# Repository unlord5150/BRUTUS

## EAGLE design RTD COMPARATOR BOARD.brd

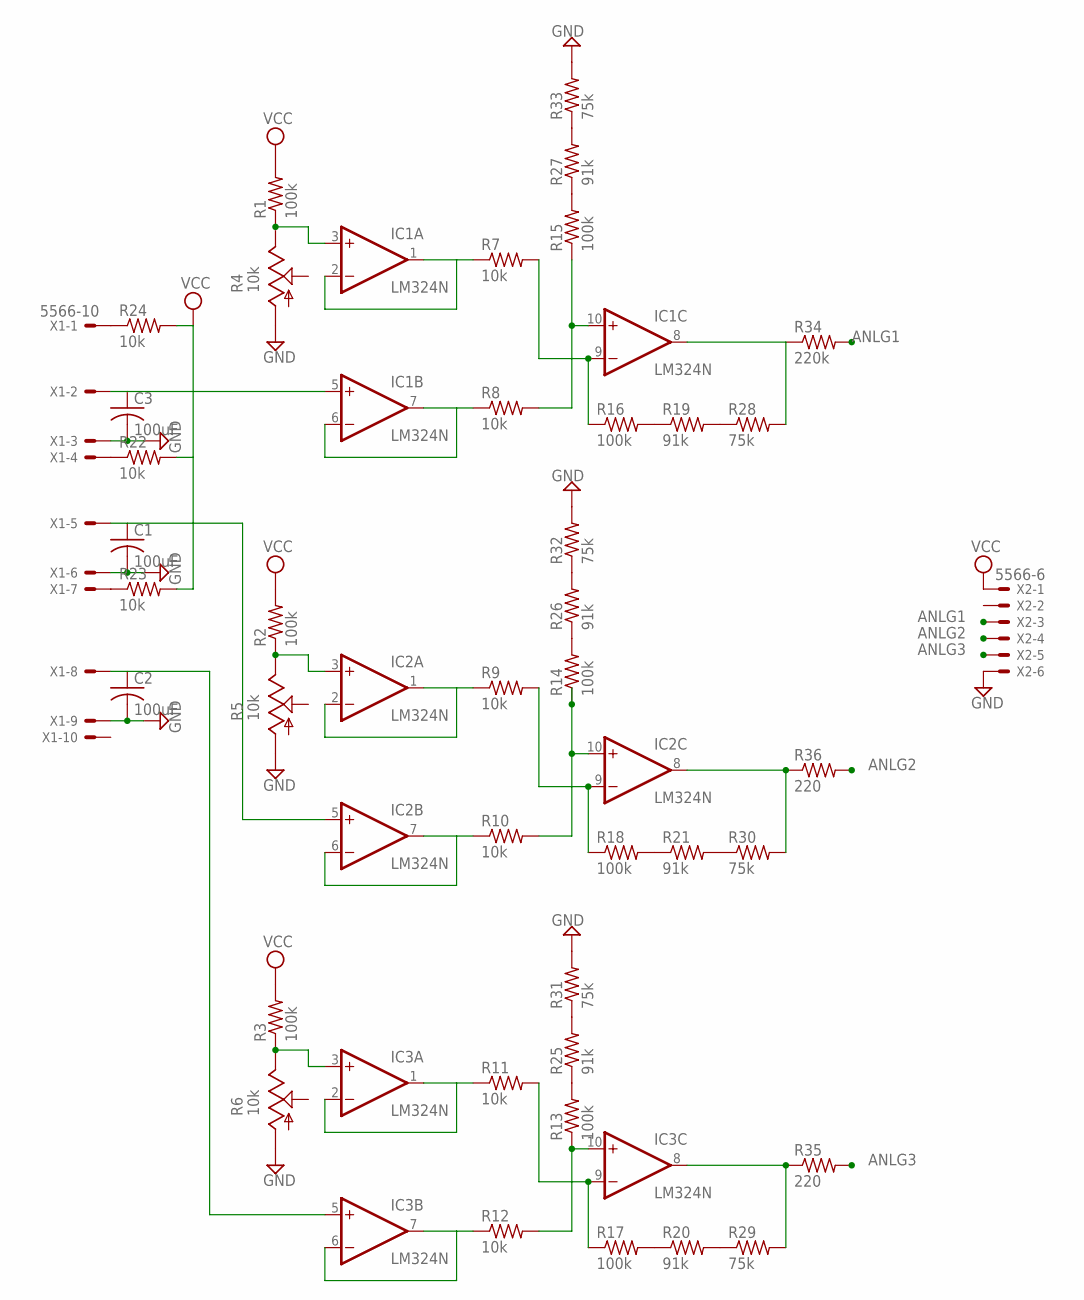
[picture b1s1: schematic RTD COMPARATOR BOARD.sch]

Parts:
C1, C2, C3: 100uF; C025-025X050
IC1, IC2, IC3: LM324N; DIL14
R1, R2, R3, R13, R14, R15, R16, R17, R18: 100k; 0204V
R4, R5, R6: 10k; B25P
R7, R8, R9, R10, R11, R12, R22, R23, R24: 10k; 0204V
R19, R20, R21, R25, R26, R27: 91k; 0204V
R28, R29, R30, R31, R32, R33: 75k; 0204V
R34: 220k; 0204V
R35, R36: 220; 0204V
X1: 5566-10
X2: 5566-6

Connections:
ANLG1: R34.2, X2.3
ANLG2: R36.2, X2.4
ANLG3: R35.2, X2.5
GND: C1.2, C2.2, C3.2, R4.A, R5.A, R6.A, R31.2, R32.2, R33.2, X1.3, X1.6, X1.9, X2.6
unnamed: R21.2, R30.1
unnamed: R18.2, R21.1
unnamed: R24.1, X1.1
unnamed: R22.1, X1.4
unnamed: R20.2, R29.1
unnamed: R17.2, R20.1
unnamed: R14.2, R26.1
unnamed: R26.2, R32.1
unnamed: IC2.3 (+IN), R2.1, R5.E
unnamed: R23.1, X1.7
unnamed: R13.2, R25.1
unnamed: IC1.3 (+IN), R1.1, R4.E
unnamed: C1.1, X1.5
unnamed: IC2.1 (OUT), IC2.2 (-IN), R9.1
unnamed: IC2.9 (-IN), R9.2, R18.1
unnamed: R25.2, R31.1
unnamed: IC1.9 (-IN), R7.2, R16.1
unnamed: IC1.1 (OUT), IC1.2 (-IN), R7.1
unnamed: IC2.6 (-IN), IC2.7 (OUT), R10.1
unnamed: IC1.6 (-IN), IC1.7 (OUT), R8.1
unnamed: IC1.10 (+IN), R8.2, R15.1
unnamed: IC1.8 (OUT), R28.2, R34.1
unnamed: C3.1, IC1.5 (+IN), X1.2
unnamed: IC2.10 (+IN), R10.2, R14.1
unnamed: R19.2, R28.1
unnamed: R16.2, R19.1
unnamed: IC2.8 (OUT), R30.2, R36.1
unnamed: R15.2, R27.1
unnamed: R27.2, R33.1
unnamed: IC3.3 (+IN), R3.1, R6.E
unnamed: IC3.1 (OUT), IC3.2 (-IN), R11.1
unnamed: IC3.9 (-IN), R11.2, R17.1
unnamed: IC3.6 (-IN), IC3.7 (OUT), R12.1
unnamed: IC3.10 (+IN), R12.2, R13.1
unnamed: IC3.8 (OUT), R29.2, R35.1
V+: IC1.4 (V+), IC2.4 (V+), IC3.4 (V+)
V-: IC1.11 (V-), IC2.11 (V-), IC3.11 (V-)
VCC: R1.2, R2.2, R3.2, R22.2, R23.2, R24.2, X2.1

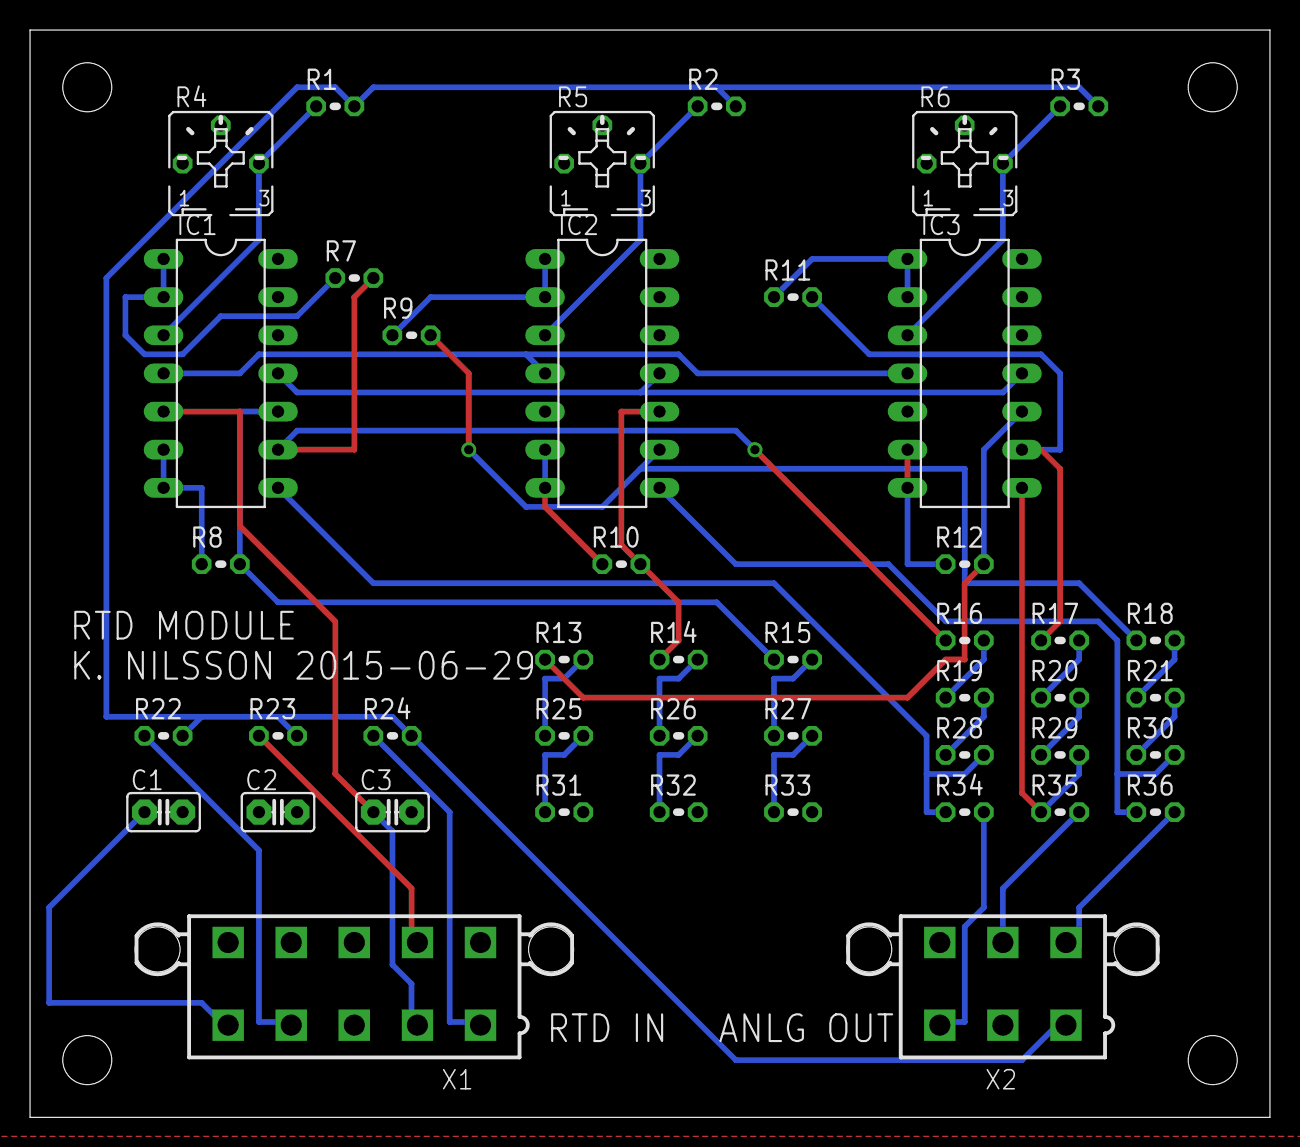
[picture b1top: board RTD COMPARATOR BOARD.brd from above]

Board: 2 copper layers, 82.5 x 72.4 mm, 44 parts (0 on the bottom side), 42 nets.

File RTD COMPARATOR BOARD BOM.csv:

"Part";"Value";"Device";"Package";"Description";"MF";"MPN";"OC_FARNELL";"OC_NEWARK";
"C1";"100uF";"C-US025-025X050";"C025-025X050";"CAPACITOR, American symbol";"";"";"";"";
"C2";"100uF";"C-US025-025X050";"C025-025X050";"CAPACITOR, American symbol";"";"";"";"";
"C3";"100uF";"C-US025-025X050";"C025-025X050";"CAPACITOR, American symbol";"";"";"";"";
"IC1";"LM324N";"LM324N";"DIL14";"OP AMP";"";"";"";"";
"IC2";"LM324N";"LM324N";"DIL14";"OP AMP";"";"";"";"";
"IC3";"LM324N";"LM324N";"DIL14";"OP AMP";"";"";"";"";
"IC4";"LM324N";"LM324N";"DIL14";"OP AMP";"";"";"";"";
"IC5";"LM324N";"LM324N";"DIL14";"OP AMP";"";"";"";"";
"IC6";"LM324N";"LM324N";"DIL14";"OP AMP";"";"";"";"";
"IC7";"LM324N";"LM324N";"DIL14";"OP AMP";"";"";"";"";
"IC8";"LM324N";"LM324N";"DIL14";"OP AMP";"";"";"";"";
"IC9";"LM324N";"LM324N";"DIL14";"OP AMP";"";"";"";"";
"R1";"100k";"R-US_0204/2V";"0204V";"RESISTOR, American symbol";"";"";"";"";
"R2";"100k";"R-US_0204/2V";"0204V";"RESISTOR, American symbol";"";"";"";"";
"R3";"100k";"R-US_0204/2V";"0204V";"RESISTOR, American symbol";"";"";"";"";
"R4";"10k";"TRIM_US-B25P";"B25P";"POTENTIOMETER";"";"";"";"";
"R5";"10k";"TRIM_US-B25P";"B25P";"POTENTIOMETER";"";"";"";"";
"R6";"10k";"TRIM_US-B25P";"B25P";"POTENTIOMETER";"";"";"";"";
"R7";"10k";"R-US_0204/2V";"0204V";"RESISTOR, American symbol";"";"";"";"";
"R8";"10k";"R-US_0204/2V";"0204V";"RESISTOR, American symbol";"";"";"";"";
"R9";"10k";"R-US_0204/2V";"0204V";"RESISTOR, American symbol";"";"";"";"";
"R10";"10k";"R-US_0204/2V";"0204V";"RESISTOR, American symbol";"";"";"";"";
"R11";"10k";"R-US_0204/2V";"0204V";"RESISTOR, American symbol";"";"";"";"";
"R12";"10k";"R-US_0204/2V";"0204V";"RESISTOR, American symbol";"";"";"";"";
"R13";"100k";"R-US_0204/2V";"0204V";"RESISTOR, American symbol";"";"";"";"";
"R14";"100k";"R-US_0204/2V";"0204V";"RESISTOR, American symbol";"";"";"";"";
"R15";"100k";"R-US_0204/2V";"0204V";"RESISTOR, American symbol";"";"";"";"";
"R16";"100k";"R-US_0204/2V";"0204V";"RESISTOR, American symbol";"";"";"";"";
"R17";"100k";"R-US_0204/2V";"0204V";"RESISTOR, American symbol";"";"";"";"";
"R18";"100k";"R-US_0204/2V";"0204V";"RESISTOR, American symbol";"";"";"";"";
"R19";"91k";"R-US_0204/2V";"0204V";"RESISTOR, American symbol";"";"";"";"";
"R20";"91k";"R-US_0204/2V";"0204V";"RESISTOR, American symbol";"";"";"";"";
"R21";"91k";"R-US_0204/2V";"0204V";"RESISTOR, American symbol";"";"";"";"";
"R22";"1k";"R-US_0204/2V";"0204V";"RESISTOR, American symbol";"";"";"";"";
"R23";"1k";"R-US_0204/2V";"0204V";"RESISTOR, American symbol";"";"";"";"";
"R24";"1k";"R-US_0204/2V";"0204V";"RESISTOR, American symbol";"";"";"";"";
"R25";"91k";"R-US_0204/2V";"0204V";"RESISTOR, American symbol";"";"";"";"";
"R26";"91k";"R-US_0204/2V";"0204V";"RESISTOR, American symbol";"";"";"";"";
"R27";"91k";"R-US_0204/2V";"0204V";"RESISTOR, American symbol";"";"";"";"";
"R28";"75k";"R-US_0204/2V";"0204V";"RESISTOR, American symbol";"";"";"";"";
"R29";"75k";"R-US_0204/2V";"0204V";"RESISTOR, American symbol";"";"";"";"";
"R30";"75k";"R-US_0204/2V";"0204V";"RESISTOR, American symbol";"";"";"";"";
"R31";"75k";"R-US_0204/2V";"0204V";"RESISTOR, American symbol";"";"";"";"";
"R32";"75k";"R-US_0204/2V";"0204V";"RESISTOR, American symbol";"";"";"";"";
"R33";"75k";"R-US_0204/2V";"0204V";"RESISTOR, American symbol";"";"";"";"";
"R34";"220";"R-US_0204/2V";"0204V";"RESISTOR, American symbol";"";"";"";"";
"R35";"220";"R-US_0204/2V";"0204V";"RESISTOR, American symbol";"";"";"";"";
"R36";"220";"R-US_0204/2V";"0204V";"RESISTOR, American symbol";"";"";"";"";
"X1";"5566-10";"5566-10";"5566-10";"Mini FIT connector 10 pol";"";"";"unknown";"unknown";
"X2";"5566-6";"5566-6";"5566-6";"Mini FIT connector 6 pol";"";"95566-61002";"unknown";"22K8620";

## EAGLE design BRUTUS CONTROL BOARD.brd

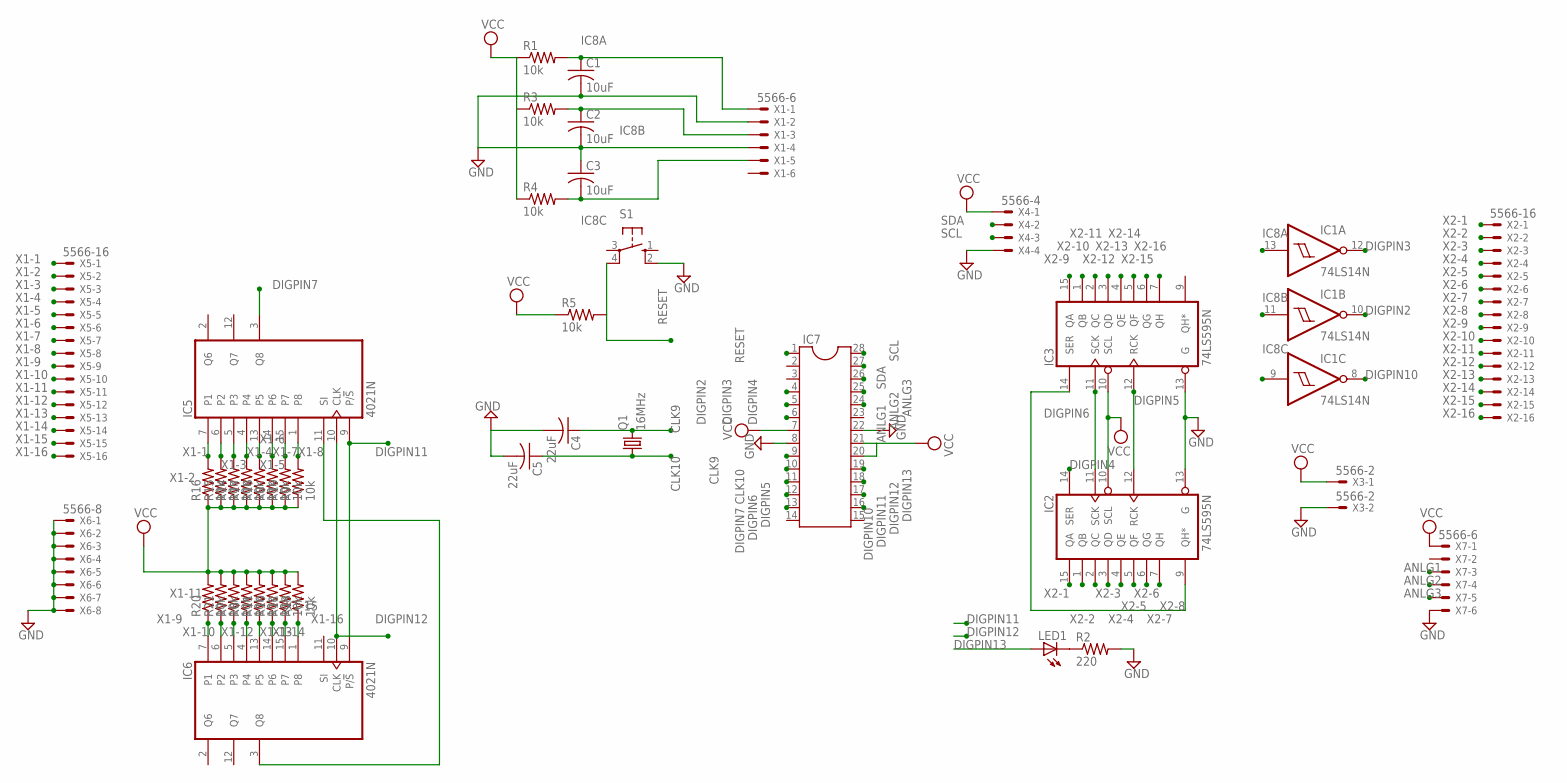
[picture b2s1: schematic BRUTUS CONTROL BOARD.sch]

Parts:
C1, C2, C3: 10uF; C025-025X050
C4, C5: 22uF; C025-025X050
IC1: 74LS14N; DIL14
IC2, IC3: 74LS595N; DIL16
IC5, IC6: 4021N; DIL16
IC7: DIL28-3
LED1: LED5MM
Q1: 16MHz; HC49/S
R1, R3, R4, R5, R6, R7, R8, R9, R10, R11, R12, R13, R14, R15, R16, R17, R18, R19, R20, R21: 10k; 0204V
R2: 220; 0204V
S1: 40-XX; B3F-40XX
X1, X7: 5566-6
X2, X5: 5566-16
X3: 5566-2
X4: 5566-4
X6: 5566-8

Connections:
ANLG1: IC7.24, X7.3
ANLG2: IC7.25, X7.4
ANLG3: IC7.26, X7.5
CLK9: C4.1, IC7.9, Q1.2
CLK10: C5.1, IC7.10, Q1.1
DIGPIN2: IC1.10 (O), IC7.4
DIGPIN3: IC1.12 (O), IC7.5
DIGPIN4: IC2.14 (SER), IC7.6
DIGPIN5: IC2.12 (RCK), IC3.12 (RCK), IC7.11
DIGPIN6: IC2.11 (SCK), IC3.11 (SCK), IC7.12
DIGPIN7: IC5.3 (Q8), IC7.13
DIGPIN10: IC1.8 (O), IC7.16
DIGPIN11: IC5.9 (P/!S), IC6.9 (P/!S), IC7.17
DIGPIN12: IC5.10 (CLK), IC6.10 (CLK), IC7.18
DIGPIN13: IC7.19, LED1.A
GND: C1.2, C2.2, C3.1, C4.2, C5.2, IC1.7 (GND), IC2.8 (GND), IC2.13 (G), IC3.8 (GND), IC3.13 (G), IC7.8, IC7.22, R2.2, S1.2 (S1), X1.2, X1.4, X3.2, X4.4, X6.1, X6.2, X6.3, X6.4, X6.5, X6.6, X6.7, X6.8, X7.6
IC8A: C1.1, IC1.13 (I), R1.2, X1.1
IC8B: C2.1, IC1.11 (I), R3.2, X1.3
IC8C: C3.2, IC1.9 (I), R4.2, X1.5
unnamed: LED1.K (C), R2.1
unnamed: IC2.9 (QH*), IC3.14 (SER)
unnamed: IC5.11 (SI), IC6.3 (Q8)
RESET: IC7.1, R5.2, S1.4 (P1)
SCL: IC7.28, X4.3
SDA: IC7.27, X4.2
VCC: IC1.14 (VCC), IC2.16 (VCC), IC3.10 (SCL), IC3.16 (VCC), IC7.7, IC7.20, IC7.21, R1.1, R4.1, R5.1, R6.2, R7.2, R8.1, R9.1, R10.2, R11.2, R12.2, R13.2, R14.1, R15.1, R16.1, R17.1, R18.1, R19.1, R20.2, R21.2, X3.1, X4.1, X7.1
VDD: IC5.16 (VDD), IC6.16 (VDD)
VSS: IC5.8 (VSS), IC6.8 (VSS)
X1-1: IC5.7 (P1), R16.2, X5.1
X1-2: IC5.6 (P2), R15.2, X5.2
X1-3: IC5.5 (P3), R14.2, X5.3
X1-4: IC5.4, R17.2, X5.4
X1-5: IC5.13 (P5), R18.2, X5.5
X1-6: IC5.14 (P6), R8.2, X5.6
X1-7: IC5.15 (P7), R19.2, X5.7
X1-8: IC5.1 (P8), R9.2, X5.8
X1-9: IC6.7 (P1), R20.1, X5.9
X1-10: IC6.6 (P2), R21.1, X5.10
X1-11: IC6.5 (P3), R7.1, X5.11
X1-12: IC6.4, R6.1, X5.12
X1-13: R11.1, X5.13
X1-14: IC6.14 (P6), R10.1, X5.14
X1-15: IC6.15 (P7), R12.1, X5.15
X1-16: IC6.1 (P8), R13.1, X5.16
X2-1: IC2.15 (QA), X2.1
X2-2: IC2.1 (QB), X2.2
X2-3: IC2.2 (QC), X2.3
X2-4: IC2.3 (QD), X2.4
X2-5: IC2.4 (QE), X2.5
X2-6: IC2.5 (QF), X2.6
X2-7: IC2.6 (QG), X2.7
X2-8: IC2.7 (QH), X2.8
X2-9: IC3.15 (QA), X2.9
X2-10: IC3.1 (QB), X2.10
X2-11: IC3.2 (QC), X2.11
X2-12: IC3.3 (QD), X2.12
X2-13: IC3.4 (QE), X2.13
X2-14: IC3.5 (QF), X2.14
X2-15: IC3.6 (QG), X2.15
X2-16: IC3.7 (QH), X2.16

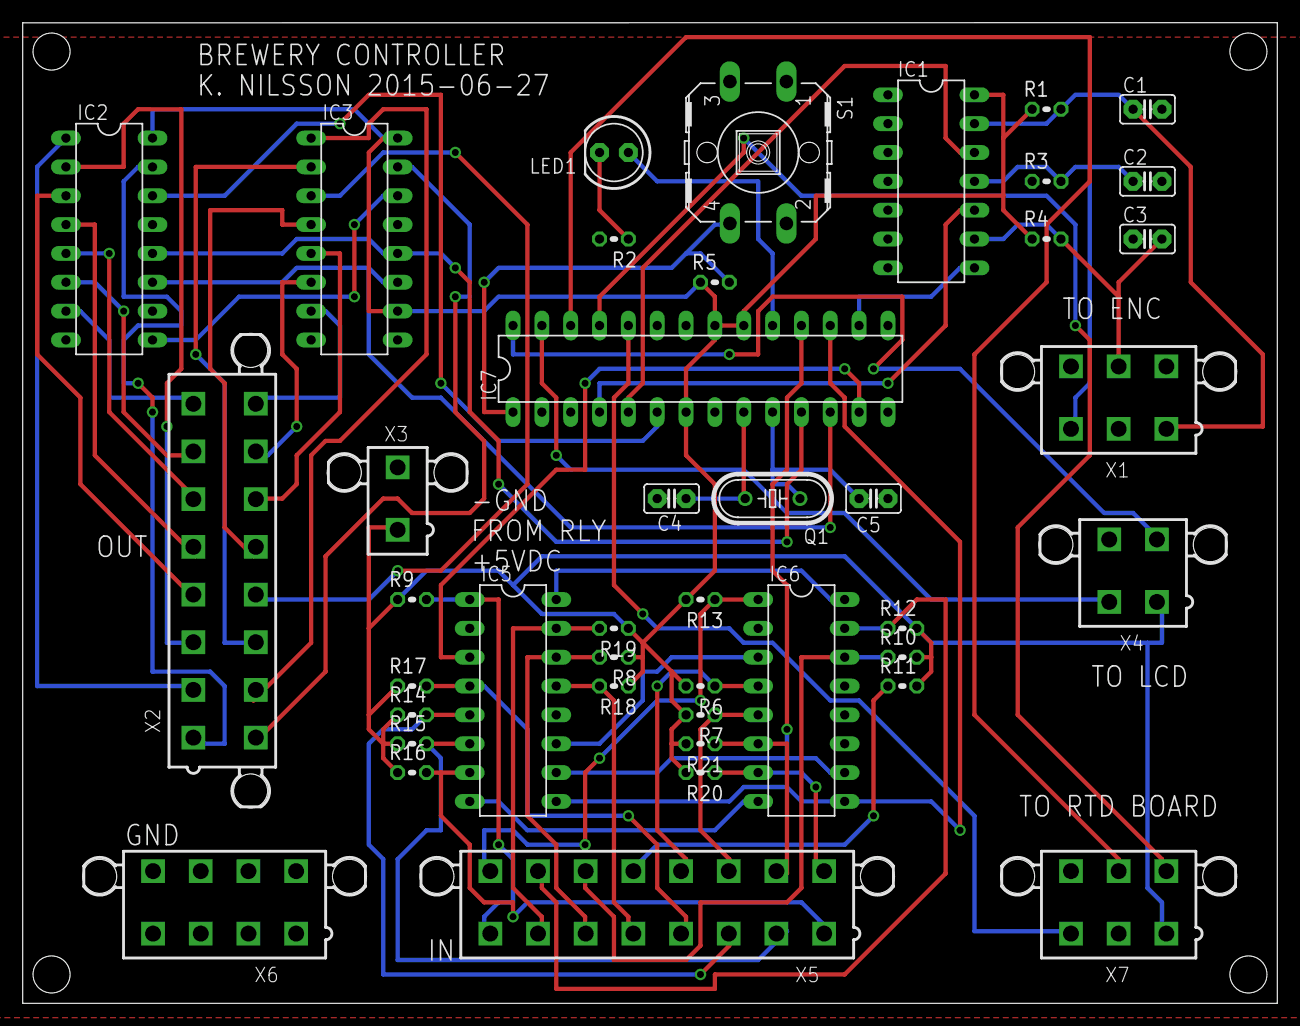
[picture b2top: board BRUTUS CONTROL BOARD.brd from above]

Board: 2 copper layers, 110.5 x 86.4 mm, 42 parts (0 on the bottom side), 60 nets.

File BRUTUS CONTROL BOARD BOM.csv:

"Part";"Value";"Device";"Package";"Description";"MF";"MPN";"OC_FARNELL";"OC_NEWARK";
"C1";"22uF";"C-US025-025X050";"C025-025X050";"CAPACITOR, American symbol";"";"";"";"";
"C2";"22uF";"C-US025-025X050";"C025-025X050";"CAPACITOR, American symbol";"";"";"";"";
"C3";"10uF";"C-US025-025X050";"C025-025X050";"CAPACITOR, American symbol";"";"";"";"";
"C4";"10uF";"C-US025-025X050";"C025-025X050";"CAPACITOR, American symbol";"";"";"";"";
"C5";"10uF";"C-US025-025X050";"C025-025X050";"CAPACITOR, American symbol";"";"";"";"";
"IC1";"ATMEGA168PROUND";"ATMEGA168PROUND";"DIL28-3-ROUND";"MICROCONTROLLER";"";"";"";"";
"IC4";"74LS595N";"74LS595N";"DIL16";"8-bit SHIFT REGISTER, output latch";"";"";"";"";
"IC5";"74LS595N";"74LS595N";"DIL16";"8-bit SHIFT REGISTER, output latch";"";"";"";"";
"IC6";"4021N";"4021N";"DIL16";"8-bit static SHIFT REGISTER";"";"";"";"";
"IC7";"4021N";"4021N";"DIL16";"8-bit static SHIFT REGISTER";"";"";"";"";
"IC8";"74LS14N";"74LS14N";"DIL14";"Hex schmitt trigger INVERTER";"";"";"";"";
"LED1";"";"LED5MM";"LED5MM";"LED";"";"";"";"";
"Q1";"16MHz";"CRYSTALHC49S";"HC49/S";"CRYSTAL";"";"";"1667008";"unknown";
"R1";"10k";"R-US_0204/2V";"0204V";"RESISTOR, American symbol";"";"";"";"";
"R2";"10k";"R-US_0204/2V";"0204V";"RESISTOR, American symbol";"";"";"";"";
"R3";"220";"R-US_0204/2V";"0204V";"RESISTOR, American symbol";"";"";"";"";
"R4";"10k";"R-US_0204/2V";"0204V";"RESISTOR, American symbol";"";"";"";"";
"R5";"10k";"R-US_0204/2V";"0204V";"RESISTOR, American symbol";"";"";"";"";
"R6";"10k";"R-US_0204/2V";"0204V";"RESISTOR, American symbol";"";"";"";"";
"R7";"10k";"R-US_0204/2V";"0204V";"RESISTOR, American symbol";"";"";"";"";
"R8";"10k";"R-US_0204/2V";"0204V";"RESISTOR, American symbol";"";"";"";"";
"R9";"10k";"R-US_0204/2V";"0204V";"RESISTOR, American symbol";"";"";"";"";
"R10";"10k";"R-US_0204/2V";"0204V";"RESISTOR, American symbol";"";"";"";"";
"R11";"10k";"R-US_0204/2V";"0204V";"RESISTOR, American symbol";"";"";"";"";
"R12";"10k";"R-US_0204/2V";"0204V";"RESISTOR, American symbol";"";"";"";"";
"R13";"10k";"R-US_0204/2V";"0204V";"RESISTOR, American symbol";"";"";"";"";
"R15";"10k";"R-US_0204/2V";"0204V";"RESISTOR, American symbol";"";"";"";"";
"R16";"10k";"R-US_0204/2V";"0204V";"RESISTOR, American symbol";"";"";"";"";
"R17";"10k";"R-US_0204/2V";"0204V";"RESISTOR, American symbol";"";"";"";"";
"R18";"10k";"R-US_0204/2V";"0204V";"RESISTOR, American symbol";"";"";"";"";
"R19";"10k";"R-US_0204/2V";"0204V";"RESISTOR, American symbol";"";"";"";"";
"R20";"10k";"R-US_0204/2V";"0204V";"RESISTOR, American symbol";"";"";"";"";
"R21";"10k";"R-US_0204/2V";"0204V";"RESISTOR, American symbol";"";"";"";"";
"R22";"10k";"R-US_0204/2V";"0204V";"RESISTOR, American symbol";"";"";"";"";
"S1";"SPST";"SPST";"JUDCOSPST";"Judco 50-0015-00";"";"";"";"";
"X1";"5566-16";"5566-16";"5566-16";"Mini FIT connector 16 pol";"";"";"unknown";"unknown";
"X2";"5566-16";"5566-16";"5566-16";"Mini FIT connector 16 pol";"";"";"unknown";"unknown";
"X3";"5566-2";"5566-2";"5566-2";"Mini FIT connector 2 pol";"";"";"1822072";"unknown";
"X4";"5566-6";"5566-6";"5566-6";"Mini FIT connector 6 pol";"";"95566-61002";"unknown";"22K8620";
"X5";"5566-6";"5566-6";"5566-6";"Mini FIT connector 6 pol";"";"95566-61002";"unknown";"22K8620";
"X6";"5566-8";"5566-8";"5566-8";"Mini FIT connector 8 pol";"";"";"unknown";"unknown";
"X7";"5566-4";"5566-4";"5566-4";"Mini FIT connector 4 pol";"";"";"unknown";"unknown";

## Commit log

2015-06-29 BRUTUS EAGLE FILES 6-28-2015
    first commit
2015-06-29 rev1
    second commit
2015-06-29 REV 2
    Changed to IC socket for ATmega328 connection
2015-06-30 BREWERY CONTROLLER SKETCH
    FIRST COMMIT
2015-06-30 4th commit
2015-07-01 First Commit
    Brewery Controller (pump on/off manual control not working, valve 1
    open/close not working)
2015-07-01 Second commit
    formatting changes, nothing works
2015-07-01 debug pump relay
    the screen now reads correctly, but shiftOUT1 is not updating
2015-07-01 p1 and v1 working
    hardware problems caused something to be all fucked. i also am
    retarded and commented out updateoutputs() during the debugging
    process, which is why shiftOUT1 wasn't updating
2015-07-01 V1 troubleshooting
    v1 does not de-energize when vcsw1 is closed
2015-07-02 shiftIN debug
    Output relays are not turning off when the valve switches activate.
2015-07-02 V1 with auto shutoff works
2015-07-02 All valves working
    Manual control on all valves works and they shut off automatically when
    the confirmation switches close. Corrected Homescreen display error
    (which valve is open)
2015-07-02 Add timer1()
    Added timer1() to end of sketch and associated variables
2015-07-02 adding comments
2015-07-04 Working on program sequence
    added runprog() and am working down the list
2015-07-07 Added conversion factor to temp input
2015-07-07 Corrections
    changed temp conversion to actually work
2015-07-10 Run program
    adding more functions to the automatic run program section
2015-07-10 Placeholders for functions done
2015-07-11 Program function done
    all program functions added, some formatting changes
2015-07-30 RTD sensor troubleshooting
2015-08-25 RTD UPDATE
    CHANGED CONSTANT FOR READING TEMP USING IA114 AND REF200 CHIPS
